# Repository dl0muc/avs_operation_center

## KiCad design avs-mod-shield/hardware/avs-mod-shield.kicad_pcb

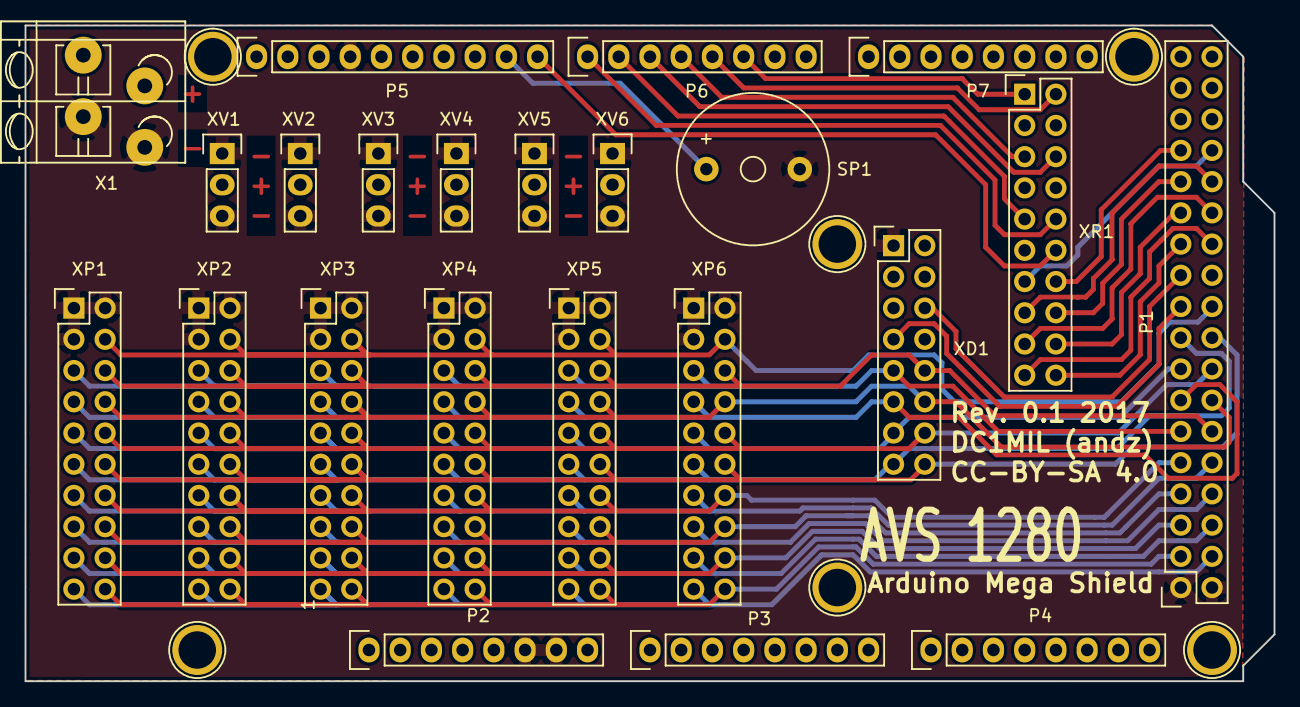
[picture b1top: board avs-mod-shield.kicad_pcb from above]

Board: 2 copper layers, 101.6 x 53.3 mm, 29 parts (0 on the bottom side), 37 nets.

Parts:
P1: Digital; Socket_Strip_Arduino_2x18
P2: Power; Socket_Strip_Arduino_1x08
P3, P4: Analog; Socket_Strip_Arduino_1x08
P5: PWM; Socket_Strip_Arduino_1x10
P6: PWM; Socket_Strip_Arduino_1x08
P7: Communication; Socket_Strip_Arduino_1x08
P8, P9, P10, P11, P12, P13: CONN_1; Arduino_1pin
SP1: SPEAKER; Buzzer_12x9.5RM7.6
X1: CONN_01X02; TerminalBlock_WAGO-804_RM5mm_2pol
XD1: CONN_02X08; Pin_Header_Straight_2x08
XP1, XP2, XP3, XP4, XP5, XP6: CONN_02X10; Pin_Header_Straight_2x10
XR1: CONN_02X10; Pin_Header_Straight_2x10
XV1, XV2, XV3, XV4, XV5, XV6: CONN_01X03; Pin_Header_Straight_1x03

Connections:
+5V: P1.35, P1.36, P2.2, P2.5, X1.1, XD1.2, XV1.2, XV2.2, XV3.2, XV4.2, XV5.2, XV6.2
//G: P1.20, XP1.4, XP2.4, XP3.4, XP4.4, XP5.4, XP6.4
/AP0: P1.3, XP1.20, XP2.20, XP3.20, XP4.20, XP5.20, XP6.20
/AP1: P1.4, XP1.19, XP2.19, XP3.19, XP4.19, XP5.19, XP6.19
/AP2: P1.5, XP1.18, XP2.18, XP3.18, XP4.18, XP5.18, XP6.18
/AP3: P1.6, XP1.17, XP2.17, XP3.17, XP4.17, XP5.17, XP6.17
/AP4: P1.7, XP1.16, XP2.16, XP3.16, XP4.16, XP5.16, XP6.16
/AP5: P1.8, XP1.15, XP2.15, XP3.15, XP4.15, XP5.15, XP6.15
/AP6: P1.9, XP1.14, XP2.14, XP3.14, XP4.14, XP5.14, XP6.14
/AP7: P1.10, XP1.13, XP2.13, XP3.13, XP4.13, XP5.13, XP6.13
/P0: P1.18, XD1.16, XP1.12, XP2.12, XP3.12, XP4.12, XP5.12, XP6.12
/P1: P1.17, XD1.15, XP1.11, XP2.11, XP3.11, XP4.11, XP5.11, XP6.11
/P2: P1.16, XD1.14, XP1.10, XP2.10, XP3.10, XP4.10, XP5.10, XP6.10
/P3: P1.15, XD1.13, XP1.9, XP2.9, XP3.9, XP4.9, XP5.9, XP6.9
/P4: P1.14, XD1.12, XP1.8, XP2.8, XP3.8, XP4.8, XP5.8, XP6.8
/P5: P1.13, XD1.11, XP1.7, XP2.7, XP3.7, XP4.7, XP5.7, XP6.7
/P6: P1.12, XD1.10, XP1.6, XP2.6, XP3.6, XP4.6, XP5.6, XP6.6
/P7: P1.11, XD1.9, XP1.5, XP2.5, XP3.5, XP4.5, XP5.5, XP6.5
/TA0: P1.30, XR1.13
/TA1: P1.29, XR1.14
/TA2: P1.28, XR1.15
/TA3: P1.27, XR1.16
/TA4: P1.26, XR1.17
/TA5: P1.25, XR1.18
/TA6: P1.24, XR1.19
/TA7: P1.23, XR1.20
/TW0: P6.6, XR1.1
/TW1: P6.5, XR1.2
/TW2: P6.4, XR1.5
/TW3: P6.3, XR1.6
/TW4: P6.2, XR1.9
/TW5: P6.1, XR1.10
/TW6: P5.10, XR1.12
BUZZER: P5.9, SP1.1
GND: P1.1, P1.2, P2.6, P2.7, P5.4, SP1.2, X1.2, XD1.1, XP1.1, XP1.2, XP1.3, XP2.1, XP2.2, XP2.3, XP3.1, XP3.2, XP3.3, XP4.1, XP4.2, XP4.3, XP5.1, XP5.2, XP5.3, XP6.1, XP6.2, XP6.3, XV1.1, XV1.3, XV2.1, XV2.3, XV3.1, XV3.3, XV4.1, XV4.3, XV5.1, XV5.3, XV6.1, XV6.3
LD1: P1.19, XD1.7
LD2: P1.21, XD1.6

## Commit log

2017-01-06 NOTICKET: Finalized Shield to Revision 0.1
    - Finalized Schematic
    - Finalized Layout
    - Created Gerber Files
    - Created pdf
2017-01-07 NOTICKET: Initial commit of firmware
    - Created initial frame for the firmware
    - Added some documentaion
2017-01-11 NOTICKET: Added Display Controller Datasheet
2017-01-11 NOTICKET: Initial commit of Display functions
    - Added Diplay Class
    - Minimal implementation including:
    - init function
    - write single character to given position
2017-01-11 NOTICKET: Added functions to display
    - Added write string function
    - Added display test to command loop
2017-01-12 NOTICKET: Fixed minor bug in avs_display.cpp
2017-01-30 NOTICKET: Changed some timings after first usage with real hardware
    - Still needs some refactoring
    - doesn't initialize sometimes
    - sometimes initializes only with one line

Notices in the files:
avs-mod-shield/hardware/avs-mod-shield.kicad_pcb:
CC-BY-SA 4.0
